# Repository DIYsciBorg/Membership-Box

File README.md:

Membership-Box
==============

A membership and donations payment box, utilizing Arduino, LCD, thermal printer and bill validator.

Arduino code: THS_Membership_Box.ino
EagleCAD files: .brd, .pro, .sch
Images of the board and schematic in png for quick viewing.

This is a membership payment and donation box. It is comprised of an Arduino with 
custom shield, 20x2 VFD display, two illuminated buttons, a thermal printer and a 
bill acceptor.

The bill acceptor is model NV10USB, by Innovative Technologies. It is programmed
to accept Japanese yen (1000, 5000, and 10000).

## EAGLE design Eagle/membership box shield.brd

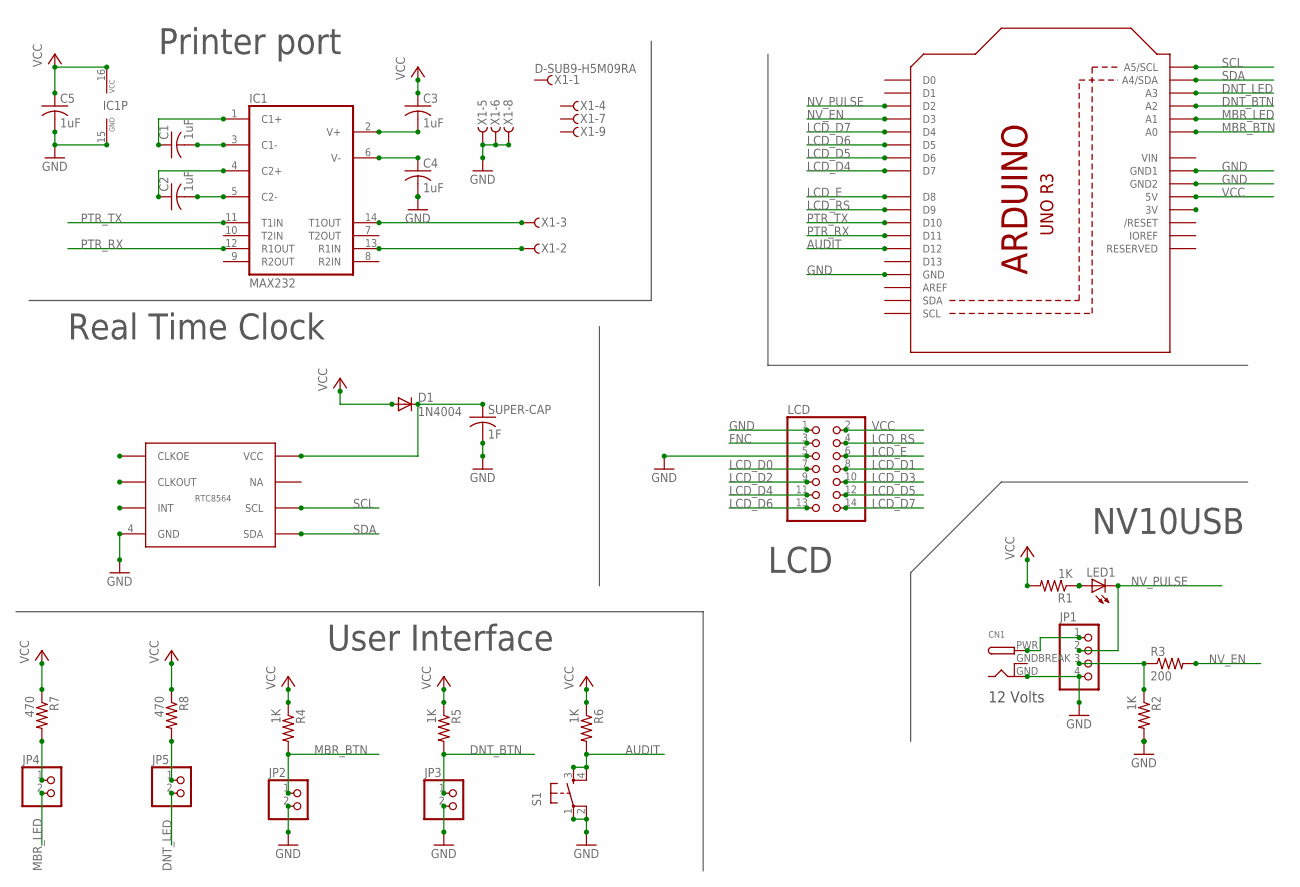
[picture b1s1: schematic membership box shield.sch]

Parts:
C1, C2, C3, C4, C5: 1uF; C025-024X044
CN1: DCBARRELPTH; DCJACK_2MM_PTH
D1: 1N4004; DO41-10
IC1: MAX232; DIL16
JP1: PINHD-1X4/90; 1X04/90
JP2, JP3, JP4, JP5: PINHD-1X2; 1X02
LCD: PINHD-2X7; 2X07
LED1: LED3MM
R1, R2, R4, R5, R6: 1K; 0204V
R3: 200; 0204V
R7, R8: 470; 0204V
RTC: RTC-8564_MODULE; DIP-8
S1: TAC_SWITCHPTH; TACTILE-PTH
SUPER-CAP: 1F; C025-024X044
U1: ARDUINOR3-DIMENSION; ARDUINOR3
X1: D-SUB9-H5M09RA; H5M09RA

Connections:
AUDIT: R6.2, S1.3, U1.D12
DNT_BTN: JP3.1, R5.2, U1.A2
DNT_LED: JP5.2, U1.A3
FNC: LCD.3
GND: C4.2, C5.2, CN1.GND, IC1.15 (GND), JP1.4, JP2.2, JP3.2, LCD.1, LCD.5, R2.2, RTC.4 (GND), S1.1, S1.2, SUPER-CAP.2, U1.GND, U1.GND1, U1.GND2, X1.5, X1.6, X1.8
GNDBREAK: CN1.GNDBREAK
LCD_D0: LCD.7
LCD_D1: LCD.8
LCD_D2: LCD.9
LCD_D3: LCD.10
LCD_D4: LCD.11, U1.D7
LCD_D5: LCD.12, U1.D6
LCD_D6: LCD.13, U1.D5
LCD_D7: LCD.14, U1.D4
LCD_E: LCD.6, U1.D8
LCD_RS: LCD.4, U1.D9
MBR_BTN: JP2.1, R4.2, U1.A0
MBR_LED: JP4.2, U1.A1
unnamed: JP1.3, R2.1, R3.1
unnamed: C1.2, IC1.3 (C1-)
unnamed: LED1.A, R1.1
unnamed: D1.C, RTC.8 (VCC), SUPER-CAP.1
unnamed: CN1.PWR, JP1.1
unnamed: C2.2, IC1.5 (C2-)
unnamed: IC1.13 (R1IN), X1.2
unnamed: JP4.1, R7.2
unnamed: JP5.1, R8.2
unnamed: C1.1, IC1.1 (C1+)
unnamed: IC1.14 (T1OUT), X1.3
unnamed: C2.1, IC1.4 (C2+)
unnamed: C3.2, IC1.2 (V+)
unnamed: C4.1, IC1.6 (V-)
NV_EN: R3.2, U1.D3
NV_PULSE: JP1.2, LED1.K (C), U1.D2
PTR_RX: IC1.12 (R1OUT), U1.D11
PTR_TX: IC1.11 (T1IN), U1.D10
SCL: RTC.6 (SCL), U1.A5 (A5/SCL)
SDA: RTC.5 (SDA), U1.A4 (A4/SDA)
VCC: C3.1, C5.1, D1.A, IC1.16 (VCC), LCD.2, R1.2, R4.1, R5.1, R6.1, R7.1, R8.1, U1.5V
VIN: U1.VIN

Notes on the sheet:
Printer port
Real Time Clock
User Interface
LCD
NV10USB
12 Volts

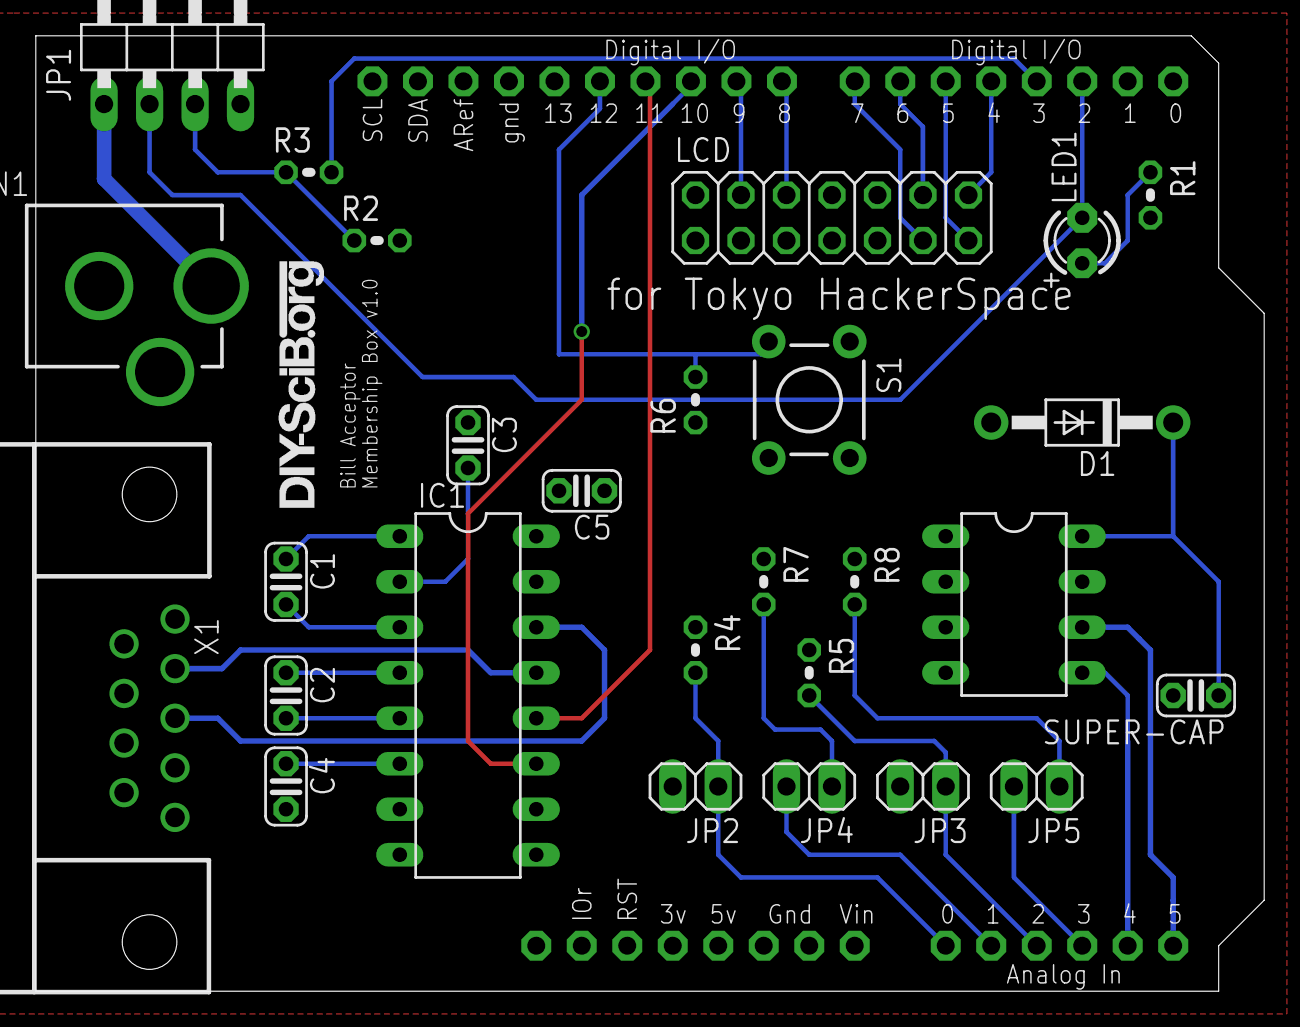
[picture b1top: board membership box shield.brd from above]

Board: 2 copper layers, 68.6 x 53.3 mm, 29 parts (0 on the bottom side), 33 nets.

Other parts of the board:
U$1: DIYSCIB.ORG-LONG

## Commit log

2013-12-09 0.9
    PCB designs fixed. Code nearly ready
2014-01-11 v1.01
    added clock support via DIYSciBorg-RTC8564 library.
    Removed the random number game.
2014-01-11 v1.01
2014-01-11 added licensing
2014-01-13 v1.042
    * Improved interrupt handling to deal with static issues
    * Corrected a receipt print routine to print the name space
2014-01-13 v1.02
    * Improved interrupt service routine to deal with static causing false
    bill inserts
    * Corrected a receipt printing routine to include the name field
2014-01-13 v1.02 proper
    * Improved ISR to deal with static causing false bill inserts
    * Corrected a print routine
2014-01-26 v1.03
    * Added printer wake
    * Added donation printing
    * Modified the audit menu
2016-09-24 update to new printer and v1.0.4 arduino ide
    fixes all new IDE issues, upgrades to new thermal printer

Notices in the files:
parts and their libraries:
SparkFun-Electromechanical: Licensing: CC v3.0 Share-Alike You are welcome to use this library for commercial purposes.
